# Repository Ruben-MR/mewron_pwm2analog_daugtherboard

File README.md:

# 🔌 Duet PWM-Analog Peripheral PCB

A compact, open-source PCB designed to interface with **Duet motherboards**, enabling reliable control of external peripheral devices requiring continuous analog control signal. This repository contains all necessary design and manufacturing files to reproduce, modify, and integrate the board into your own projects.

---

## 📌 Overview

This project provides a hardware solution for expanding the capabilities of Duet-based systems by offering:

* Clean and modular peripheral interfacing
* Reliable signal routing and power distribution
* Easy integration with existing Duet ecosystems
* Direct interface with Duet's native GPIOs to convert PWM signals into continuous analog signals 
* Support for PWM conversion to analog output in the range of 0-3.3V, 0-5V, and 0-10V, configurable via a built-in switch 

The design is fully open-source and built using **KiCad 9.0**, making it accessible for customization and further development.

---

## 📂 Repository Structure

```
├── /kicad/              # KiCad project files (.kicad_pro, .kicad_sch, .kicad_pcb)
├── /gerbers/            # Manufacturing Gerber files and ZIP file for manufacturing
├── /bom/                # Bill of Materials (CSV / ODS / PDF)
└── README.md            # Project documentation
```

---

## 🖼️ Preview

---

## 🚀 Getting Started

### 1. Clone the Repository

```bash
git clone TBD
cd duet-peripheral-pcb
```

### 2. Open in KiCad

* Install **KiCad 9.0** or newer
* Open the project file located in `/kicad/`

### 3. Review the Design

* Inspect schematic (`.kicad_sch`)
* Inspect PCB layout (`.kicad_pcb`)
* Verify design rules and connections

---

## 🏭 Manufacturing

To fabricate the PCB:

1. Navigate to the `/gerbers/` folder
2. Upload either the ZIP file, already with all of the necessary files, or the separate Gerber files and BOM. Follow the instructions of your preferred PCB manufacturer
3. Use the provided BOM (`/bom/`) for component sourcing, also included in the `/gerbers/` folder

### Recommended Checks

* Verify layer stackup compatibility
* Confirm drill sizes and tolerances
* Double-check component footprints

---

## 🧾 Bill of Materials (BOM)

The BOM includes:

* Component references
* Manufacturer part numbers
* Quantities
* Suggested suppliers

You can find it in the `/bom/` directory.

---

## 🔌 Integration with Duet

This board is designed to interface directly with Duet motherboards. Taking as an example the integration the connection with a Duet 3 Mini and an SMC 1050 pressure regulator, the wiring should be performed as shown in the diagram below.

Once connected, the GPIO should be configured manually, or upon printer initialization by adding the following lines to the config.h file of the printer (modify the port number as needed, as well as the port name to match your GPIO).

```
M950 P10 C"io2.out" Q1000
M42 P10 S0
```

The M42 is used to initialize the PWM signal of the GPIO to zero. Further M42 commands can be sent during operation to adjust on-the-fly the duty cycle of the PWM signal, and the resulting analog voltage from the board.

---

## 📜 License

This project is licensed under the **GPL-3.0 license**.

---

## 🙌 Acknowledgements

* Duet3D community
* KiCad development team

---

## 📬 Contact / Issues

For questions or collaboration:

* GitHub Issues
* E-mail: [ruben.martinrodriguez@unibas.ch](mailto:ruben.martinrodriguez@unibas.ch)

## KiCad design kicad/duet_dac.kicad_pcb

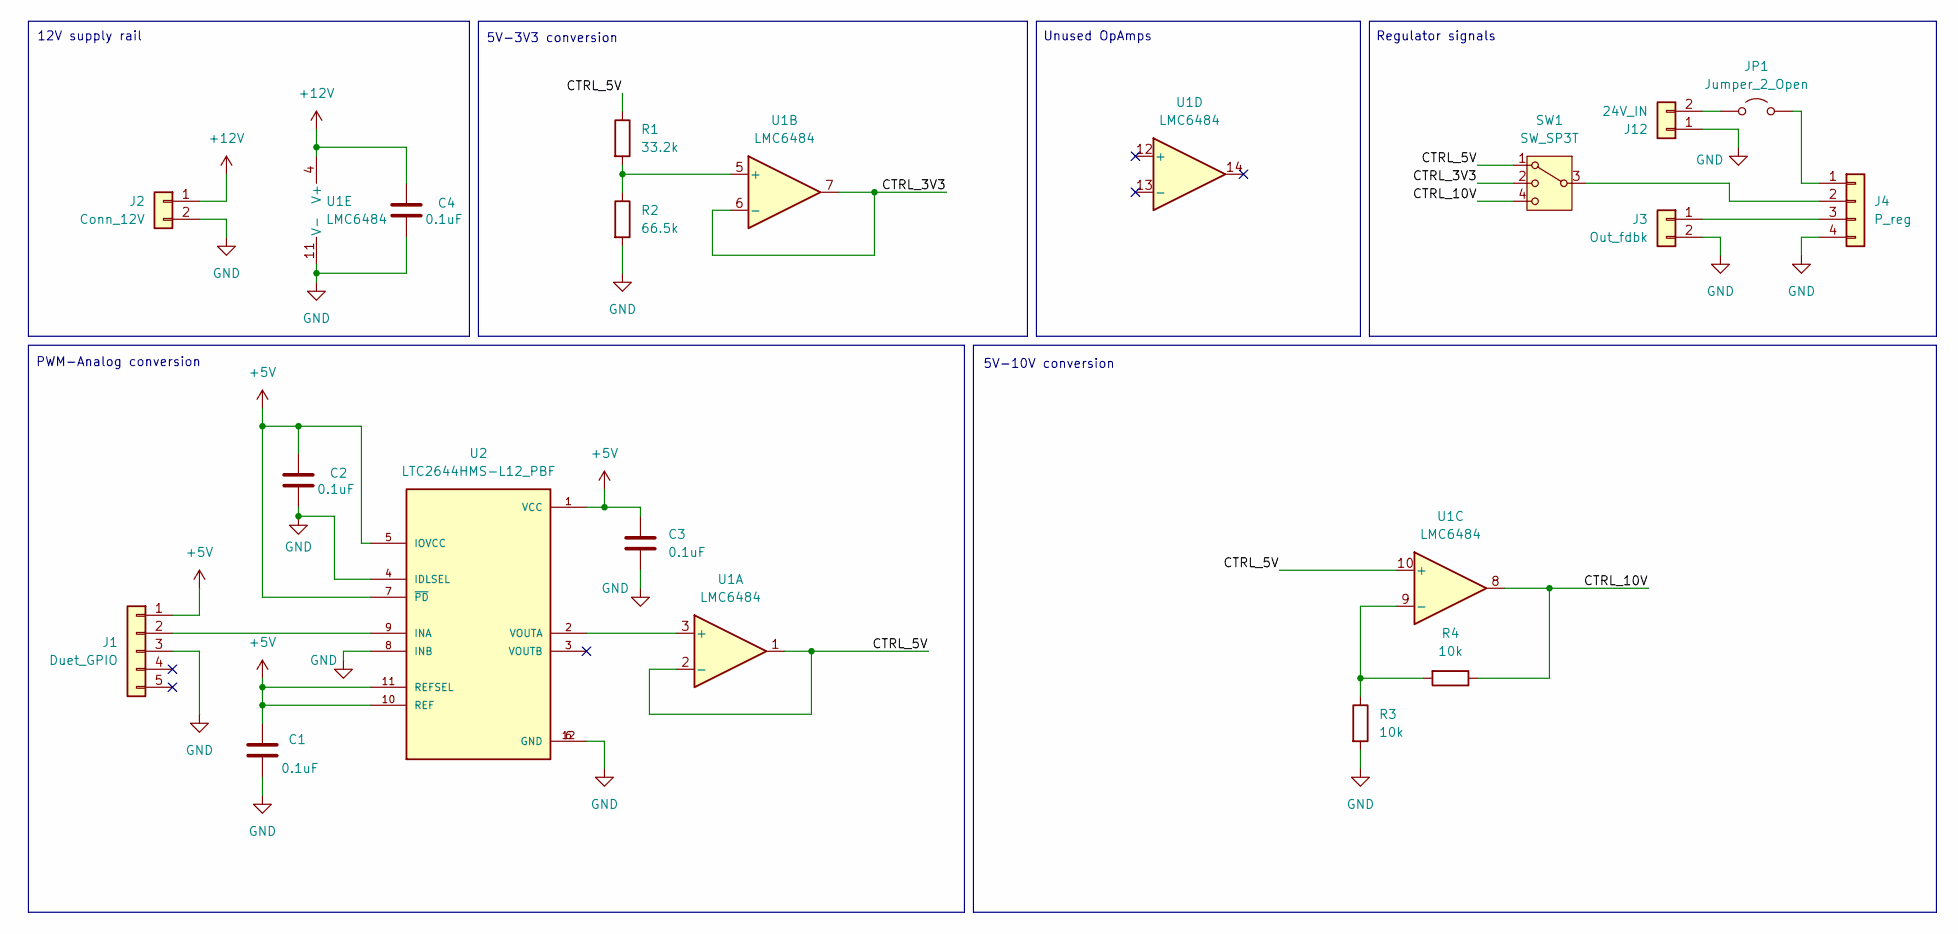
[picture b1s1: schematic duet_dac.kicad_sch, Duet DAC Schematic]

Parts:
C1, C2, C3, C4: 0.1uF; C_Rect_L4.0mm_W2.5mm_P2.50mm
J1: Duet_GPIO; Molex_KK-254_AE-6410-05A_1x05_P2.54mm_Vertical
J2: Conn_12V; Molex_KK-254_AE-6410-02A_1x02_P2.54mm_Vertical
J3: Out_fdbk; Molex_KK-254_AE-6410-02A_1x02_P2.54mm_Vertical
J4: P_reg; TerminalBlock_4Ucon_1x04_P3.50mm_Horizontal
J12: 24V_IN; Molex_KK-254_AE-6410-02A_1x02_P2.54mm_Vertical
JP1: Jumper_2_Open; PinHeader_1x02_P2.54mm_Vertical
R1: 33.2k; R_Axial_DIN0207_L6.3mm_D2.5mm_P7.62mm_Horizontal
R2: 66.5k; R_Axial_DIN0207_L6.3mm_D2.5mm_P7.62mm_Horizontal
R3, R4: 10k; R_Axial_DIN0207_L6.3mm_D2.5mm_P7.62mm_Horizontal
SW1: SW_SP3T; JSM07011
U1: LMC6484; SOIC-14_3.9x8.7mm_P1.27mm
U2: LTC2644HMS-L12_PBF; MSOP-12_3x4.039mm_P0.65mm; PARTREV B

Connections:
+5V: C1.1, C2.1, C3.1, J1.1, U2.1 (VCC), U2.5 (IOVCC), U2.7 (~PD), U2.10 (REF), U2.11 (REFSEL)
+12V: C4.1, J2.1, U1.4 (V+)
/CTRL_3V3: SW1.2, U1.6 (-), U1.7
/CTRL_5V: R1.1, SW1.1, U1.1, U1.2 (-), U1.10 (+)
/CTRL_10V: R4.1, SW1.4, U1.8
GND: C1.2, C2.2, C3.2, C4.2, J1.3, J2.2, J3.2, J4.4, J12.1, R2.2, R3.2, U1.11 (V-), U2.4 (IDLSEL), U2.6 (GND), U2.8 (INB), U2.12 (GND)
unnamed: J1.2, U2.9 (INA)
unnamed: J3.1, J4.3
unnamed: J4.1, JP1.2 (B)
unnamed: J4.2, SW1.3
unnamed: J12.2, JP1.1 (A)
unnamed: U1.3 (+), U2.2 (VOUTA)
unnamed: R1.2, R2.1, U1.5 (+)
unnamed: R3.1, R4.2, U1.9 (-)

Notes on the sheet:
5V-3V3 conversion
5V-10V conversion
Regulator signals
Unused OpAmps
12V supply rail
PWM-Analog conversion

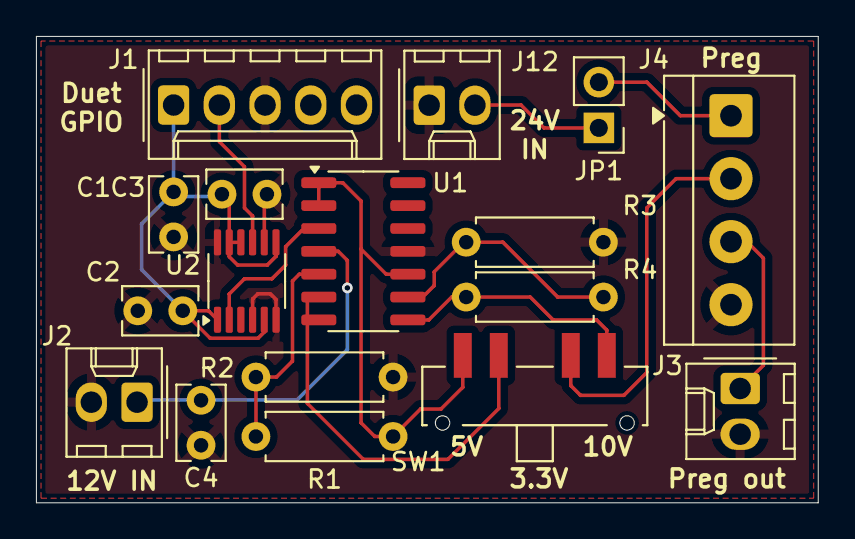
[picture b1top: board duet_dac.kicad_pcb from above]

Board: 2 copper layers, 43.4 x 25.9 mm, 17 parts (0 on the bottom side), 14 nets.

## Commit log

2026-06-29 rmr: initial commit
2026-06-29 fix README images
